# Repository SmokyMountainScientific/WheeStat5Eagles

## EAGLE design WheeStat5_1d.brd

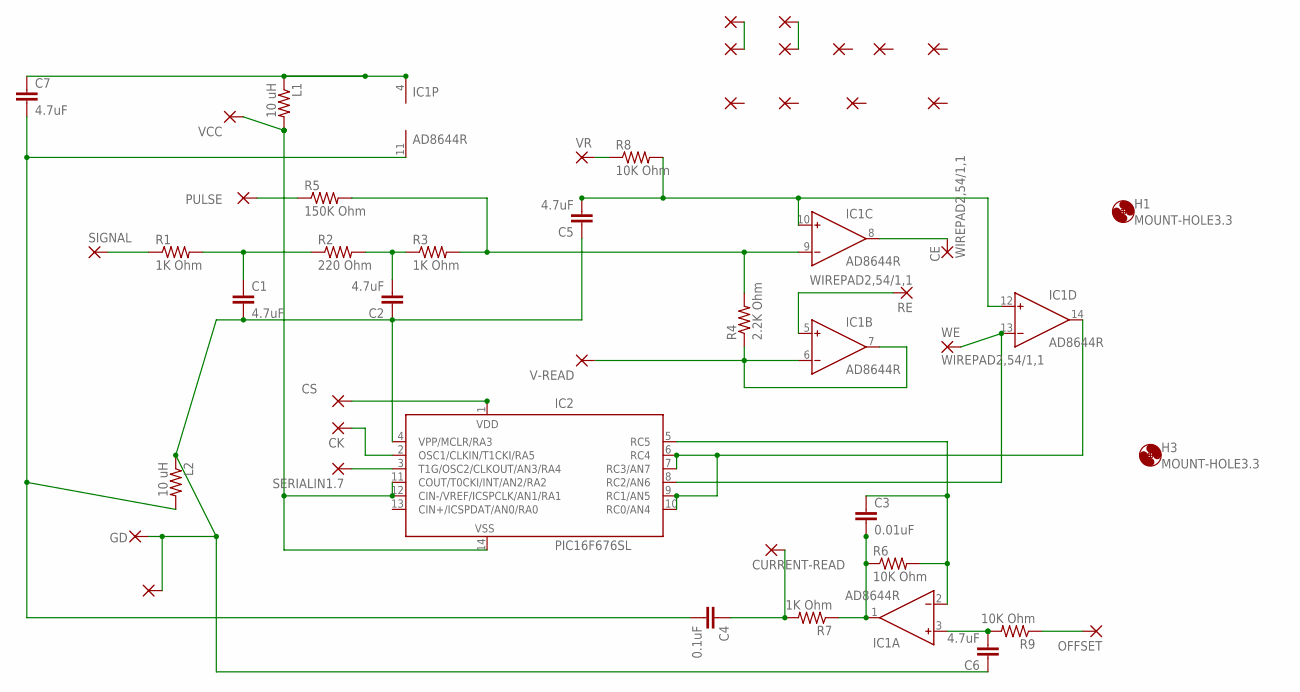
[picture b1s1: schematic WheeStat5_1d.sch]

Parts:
1, 1.1, 1.2, 1.3, 1.4, 2, 3, 4, 5, 6, 7, 8: 1,6/0,9
C1, C2, C5, C6, C7: 4.7uF; C1206K
C3: 0.01uF; C0805
C4: 0.1uF; C1206K
CE: WIREPAD2,54/1,1; 2,54/1,1
CK: 1,6/0,9
CS: 1,6/0,9
CURRENT-READ: 1,6/0,9
GD: 1,6/0,9
H1, H3: MOUNT-HOLE3.3; 3,3
IC1: AD8644R; SO14
IC2: PIC16F676SL; SO-14
L1, L2: 10 uH; R0805
OFFSET: 1,6/0,9
PULSE: 1,6/0,9
R1, R3, R7: 1K Ohm; R0805
R2: 220 Ohm; R0805
R4: 2.2K Ohm; R0805
R5: 150K Ohm; R0805
R6, R8, R9: 10K Ohm; R0805
RE: WIREPAD2,54/1,1; 2,54/1,1
SERIALIN1.7: 1,6/0,9
SIGNAL: 1,6/0,9
V-READ: 1,6/0,9
VCC: 1,6/0,9
VR: 1,6/0,9
WE: WIREPAD2,54/1,1; 2,54/1,1

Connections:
unnamed: C5.2, IC1.10 (IN+), IC1.12 (IN+), R8.2
unnamed: IC1.6 (IN-), IC1.7 (OUT), R4.1, V-READ.1
unnamed: IC1.5 (IN+), RE.1
unnamed: C4.1, CURRENT-READ.1, R7.2
unnamed: CE.1, IC1.8 (OUT)
unnamed: 1.2.1, 1.3.1
unnamed: 1.4.1, 8.1
unnamed: R1.1, SIGNAL.1
unnamed: C3.2, IC1.1 (OUT), R6.1, R7.1
unnamed: C4.2, C7.2, IC1.11 (V-), L2.2
unnamed: PULSE.1, R5.1
unnamed: C1.1, R1.2, R2.1
unnamed: 1.1.1, C1.2, C2.1, C5.1, C6.1, GD.1, IC2.4 (VPP/MCLR/RA3), L2.1
unnamed: CS.1, IC2.1 (VDD)
unnamed: IC1.13 (IN-), IC2.8 (RC2/AN6), WE.1
unnamed: IC2.11 (COUT/T0CKI/INT/AN2/RA2), IC2.12 (CIN-/VREF/ICSPCLK/AN1/RA1), IC2.14 (VSS), L1.2, VCC.1
unnamed: C2.2, R2.2, R3.1
unnamed: IC2.3 (T1G/OSC2/CLKOUT/AN3/RA4), SERIALIN1.7.1
unnamed: IC1.9 (IN-), R3.2, R4.2, R5.2
unnamed: IC1.14 (OUT), IC2.6 (RC4), IC2.7 (RC3/AN7), IC2.9 (RC1/AN5), IC2.10 (RC0/AN4)
unnamed: CK.1, IC2.2 (OSC1/CLKIN/T1CKI/RA5)
unnamed: C7.1, IC1.4 (V+), L1.1
unnamed: C6.2, IC1.3 (IN+), R9.2
unnamed: OFFSET.1, R9.1
unnamed: C3.1, IC1.2 (IN-), IC2.5 (RC5), R6.2
unnamed: R8.1, VR.1

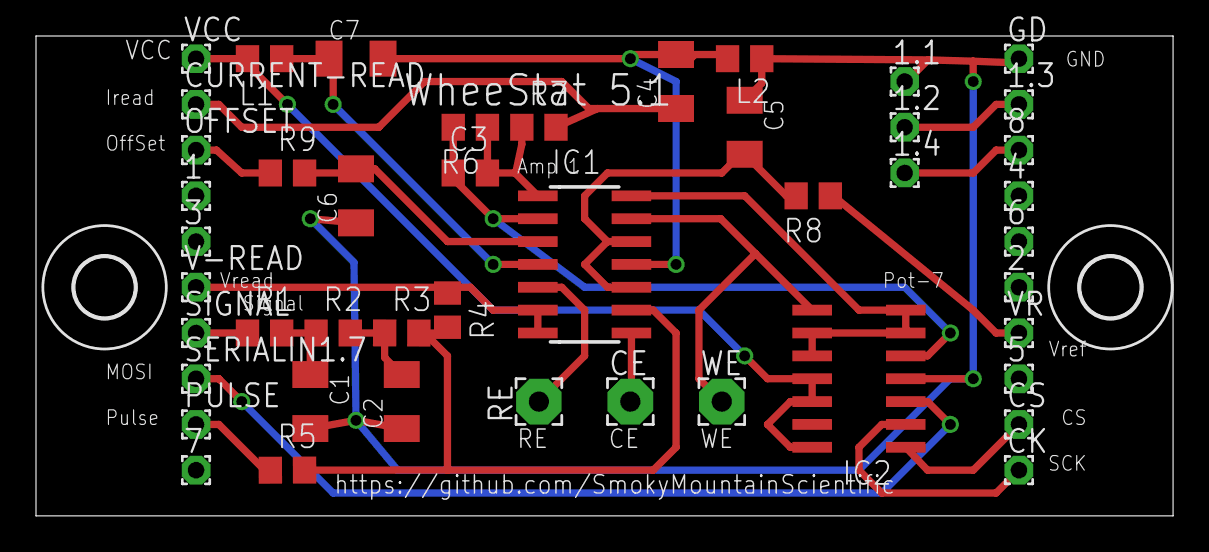
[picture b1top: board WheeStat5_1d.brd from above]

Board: 2 copper layers, 63.2 x 26.7 mm, 48 parts (0 on the bottom side), 26 nets.

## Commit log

2015-10-21 :boom::camel: Added .gitattributes & .gitignore files
2015-10-21 Eagle files for WheeStat5_1d potentiostat
    Analog amplifier board and schematic files
